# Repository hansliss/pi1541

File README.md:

# pi1541
Raspberry pi card for PI1541 with an OLED display

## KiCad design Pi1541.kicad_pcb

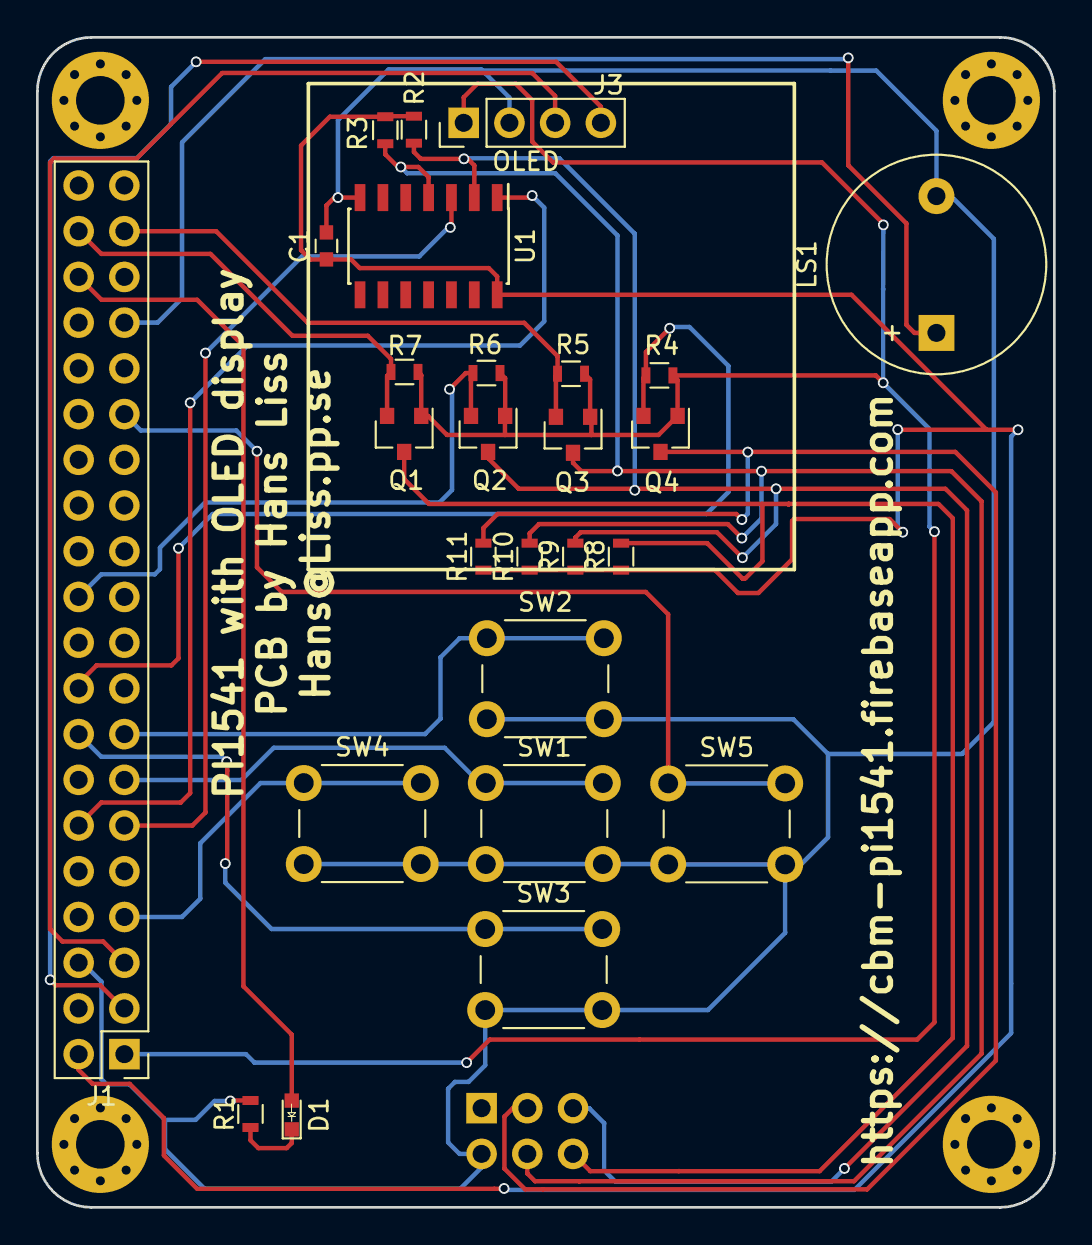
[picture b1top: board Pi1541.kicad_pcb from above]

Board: 2 copper layers, 56.5 x 65.0 mm, 27 parts (1 on the bottom side), 23 nets.

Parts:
C1: 100nf; C_0603
D1: LED; LED_0603
J1: Raspberry_Pi_2_3; Pin_Header_Straight_2x20_Pitch2.54mm
J2: DIN; Pin_Header_Straight_2x03_Pitch2.54mm
J3: OLED; Pin_Header_Straight_1x04_Pitch2.54mm
LS1: Speaker_Crystal; Buzzer_12x9.5RM7.6
Q1, Q2, Q3, Q4: BSS138; SOT-23
R1: 100; R_0603
R2, R3: 1k; R_0603
R4, R5, R6, R7, R8, R9, R10, R11: 10k; R_0603
SW1, SW2, SW3, SW4, SW5: SW_Push; SW_PUSH_6mm
U1: 74LS06; SOIC-14_3.9x8.7mm_Pitch1.27mm

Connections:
+3V3: J1.1, J3.1, Q1.1, Q2.1, Q3.1, Q4.1, R4.1, R5.1, R6.1, R7.1
+5V: C1.1, J1.2, R2.1, R3.1, R8.1, R9.1, R10.1, R11.1, U1.14
/ATN: J2.3, Q4.3, R11.2
/CLK_H: J2.4, Q3.3, R3.2, R10.2, U1.4
/CLK_L: J1.11, U1.3
/DATA_H: J2.5, Q2.3, R2.2, R9.2, U1.2
/DATA_L: J1.12, U1.1
/IN_CLK: J1.37, Q3.2, R5.2
/IN_DATA: J1.22, Q2.2, R6.2
/RST: J2.6, Q1.3, R8.2
/SCL: J1.5, J3.3
/SDA: J1.3, J3.4
GND: C1.2, J1.6, J2.2, J3.2, LS1.2, R1.2, SW1.2, SW2.2, SW3.2, SW4.2, SW5.2, U1.7
unnamed: D1.1, R1.1
unnamed: D1.2, J1.36
unnamed: J1.7, SW4.1
unnamed: J1.13, SW1.1
unnamed: J1.15, SW2.1
unnamed: J1.16, SW3.1
unnamed: J1.18, Q4.2, R4.2
unnamed: J1.29, SW5.1
unnamed: J1.33, LS1.1
unnamed: J1.38, Q1.2, R7.2

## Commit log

2018-07-10 Initial import
2018-07-19 Added notes.txt with component list
2018-07-29 Rearranged everything to correct errors Changed the buzzer footprint Replaced resistor nets with individual resistors
2018-07-31 Replaced the SIL pin header for the DIN connector with a DIL pin header
2018-08-06 Create LICENSE
